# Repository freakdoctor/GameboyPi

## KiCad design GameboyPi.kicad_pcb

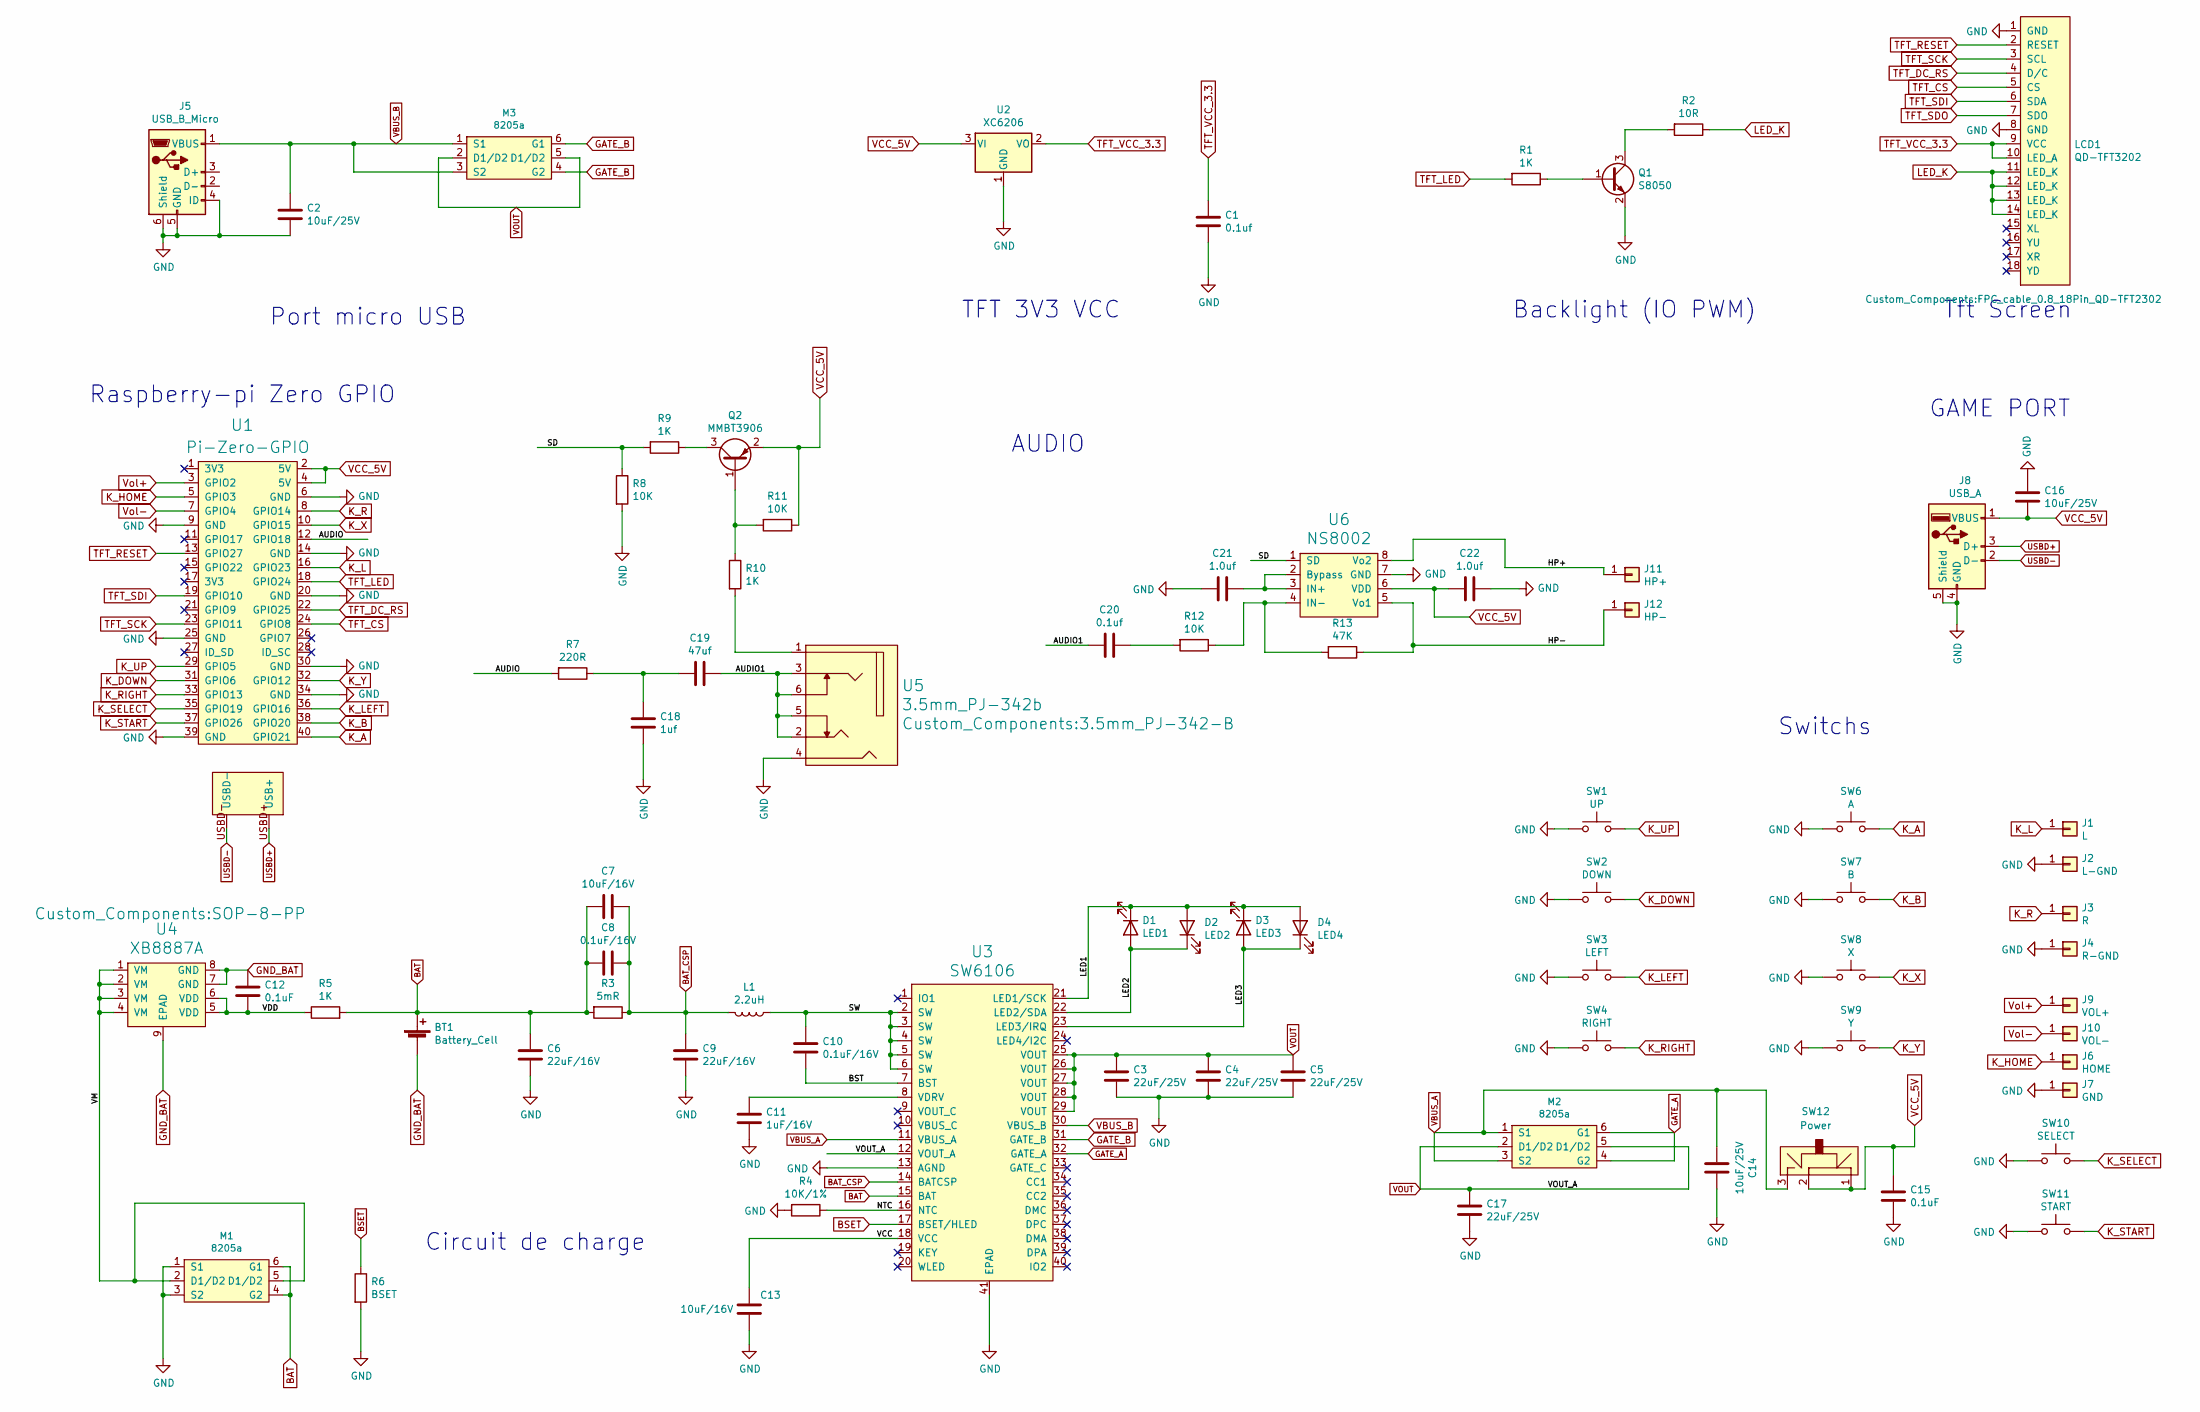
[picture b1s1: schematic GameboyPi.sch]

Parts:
BT1: Battery_Cell; Li-Po_3.7
C1: 0.1uf; C_0805_2012Metric; LCSC C286511
C2, C16: 10uF/25V; C_1206_3216Metric; LCSC C90538
C3, C4, C5, C17: 22uF/25V; C_0805_2012Metric; LCSC C90153
C6, C9: 22uF/16V; C_0805_2012Metric; LCSC C116973
C7, C13: 10uF/16V; C_0603_1608Metric; LCSC C70225
C8, C10: 0.1uF/16V; C_0603_1608Metric; LCSC C307478
C11: 1uF/16V; C_0603_1608Metric; LCSC C307478
C12: 0.1uF; C_0603_1608Metric; LCSC C307478
C14: 10uF/25V; C_1206_3216Metric; LCSC C70225
C15: 0.1uF; C_1206_3216Metric; LCSC C105213
C18: 1uf; C_0603_1608Metric
C19: 47uf; C_0603_1608Metric
C20: 0.1uf; C_0603_1608Metric
C21, C22: 1.0uf; C_0603_1608Metric
D1: LED1; LED_0805_2012Metric; LCSC C138557
D2: LED2; LED_0805_2012Metric; LCSC C138557
D3: LED3; LED_0805_2012Metric; LCSC C138557
D4: LED4; LED_0805_2012Metric; LCSC C138557
J1: L; Pin_D1.0mm_L10.0mm_LooseFit
J2: L-GND; Pin_D1.0mm_L10.0mm_LooseFit
J3: R; Pin_D1.0mm_L10.0mm_LooseFit
J4: R-GND; Pin_D1.0mm_L10.0mm_LooseFit
J5: USB_B_Micro; USB_Micro-B_Molex_47346-0001; LCSC C132560
J6: HOME; Edge_connection
J7: GND; Edge_connection
J8: USB_A; USB_A_Molex_67643_Horizontal; LCSC C2765194
J9: VOL+; Edge_connection
J10: VOL-; Edge_connection
J11: HP+; Edge_connection
J12: HP-; Edge_connection
L1: 2.2uH; L_Abracon_ASPI-0630LR
LCD1: QD-TFT3202; FPC_cable_0.8_18Pin_QD-TFT2302
M1, M2, M3: 8205a; SOT-23-6; LCSC C2762931
Q1: S8050; SOT-23; LCSC C2146
Q2: MMBT3906; SOT-23
R1: 1K; R_0805_2012Metric; LCSC C269744
R2: 10R; R_0805_2012Metric; LCSC C17477
R3: 5mR; R_1206_3216Metric; LCSC C601096
R4: 10K/1%; R_0603_1608Metric; LCSC C116677
R5: 1K; R_0603_1608Metric; LCSC C269704
R6: BSET; R_0805_2012Metric
R7: 220R; R_0603_1608Metric
R8, R11, R12: 10K; R_0603_1608Metric
R9, R10: 1K; R_0603_1608Metric
R13: 47K; R_0603_1608Metric
SW1: UP; Kbpad
SW2: DOWN; Kbpad
SW3: LEFT; Kbpad
SW4: RIGHT; Kbpad
SW6: A; Kbpad
SW7: B; Kbpad
SW8: X; Kbpad
SW9: Y; Kbpad
SW10: SELECT; Kbpad
SW11: START; Kbpad
SW12: Power; SW_SPDT_PCM12
U1: Pi-Zero-GPIO; Pi_Zero_SMD
U2: XC6206; SOT-23; LCSC C5446
U3: SW6106; QFN-40-1EP_6x6mm_P0.5mm_EP4.6x4.6mm_ThermalVias; LCSC C406803
U4: XB8887A; SOP-8-PP
U5: 3.5mm_PJ-342b; 3.5mm_PJ-342-B
U6: NS8002; SOP-8-PP

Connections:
/AUDIO: R7.2, U1.12 (GPIO18)
/AUDIO1: C19.1, C20.2, U5.2, U5.3, U5.5, U5.6
/BST: C10.1, U3.7 (BST)
/HP+: J11.1, U6.8 (Vo2); also elsewhere on the board
/HP-: J12.1, R13.1, U6.5 (Vo1); also elsewhere on the board
/LED1: D1.1 (K), D2.2 (A), D3.1 (K), D4.2 (A), U3.21 (LED1/SCK)
/LED2: D1.2 (A), D2.1 (K), U3.22 (LED2/SDA)
/LED3: D3.2 (A), D4.1 (K), U3.23 (LED3/IRQ)
/NTC: R4.1, U3.16 (NTC)
/SD: R8.1, R9.2, U6.1 (SD)
/SW: C10.2, L1.1, U3.2 (SW), U3.3 (SW), U3.4 (SW), U3.5 (SW), U3.6 (SW)
/VCC: C13.2, U3.18 (VCC)
/VDD: C12.2, R5.1, U4.5 (VDD), U4.6 (VDD)
/VM: M1.2 (D1/D2), M1.5 (D1/D2), U4.1 (VM), U4.2 (VM), U4.3 (VM), U4.4 (VM)
BAT: BT1.1 (+), C6.1, C7.2, C8.2, M1.4 (G2), M1.6 (G1), R3.2, R5.2, U3.15 (BAT); also elsewhere on the board
BAT_CSP: C7.1, C8.1, C9.1, L1.2, R3.1, U3.14 (BATCSP)
BSET: R6.1, U3.17 (BSET/HLED)
GATE_A: M2.4 (G2), M2.6 (G1), U3.32 (GATE_A)
GATE_B: M3.4 (G2), M3.6 (G1), U3.31 (GATE_B)
GND: C1.2, C2.2, C3.2, C4.2, C5.2, C6.2, C9.2, C11.2, C13.1, C14.1, C15.2, C16.1, C17.2, C18.1, C21.2, C22.1, J2.1, J4.1, J5.4 (ID), J5.5 (GND), J5.6 (Shield), J7.1, J8.4 (GND), J8.5 (Shield), LCD1.1 (GND), LCD1.8 (GND), M1.1 (S1), M1.3 (S2), Q1.2 (E), R4.2, R6.2, R8.2, SW1.1, SW2.1, SW3.1, SW4.1, SW6.1, SW7.1, SW8.1, SW9.1, SW10.1, SW11.1, U1.6 (GND), U1.9 (GND), U1.14 (GND), U1.20 (GND), U1.25 (GND), U1.30 (GND), U1.34 (GND), U1.39 (GND), U2.1 (GND), U3.13 (AGND), U3.41 (EPAD), U5.4, U6.7 (GND)
GND_BAT: BT1.2 (-), C12.1, U4.7 (GND), U4.8 (GND), U4.9 (EPAD); also elsewhere on the board
K_A: SW6.2, U1.40 (GPIO21)
K_B: SW7.2, U1.38 (GPIO20)
K_DOWN: SW2.2, U1.31 (GPIO6)
K_HOME: J6.1, U1.5 (GPIO3)
K_L: J1.1, U1.16 (GPIO23)
K_LEFT: SW3.2, U1.36 (GPIO16)
K_R: J3.1, U1.8 (GPIO14)
K_RIGHT: SW4.2, U1.33 (GPIO13)
K_SELECT: SW10.2, U1.35 (GPIO19)
K_START: SW11.2, U1.37 (GPIO26)
K_UP: SW1.2, U1.29 (GPIO5)
K_X: SW8.2, U1.10 (GPIO15)
K_Y: SW9.2, U1.32 (GPIO12)
LED_K: LCD1.11 (LED_K), LCD1.12 (LED_K), LCD1.13 (LED_K), LCD1.14 (LED_K), R2.1
unnamed: C11.1, U3.8 (VDRV)
unnamed: C18.2, C19.2, R7.1
unnamed: C20.1, R12.2
unnamed: C21.1, U6.2 (Bypass), U6.3 (IN+)
unnamed: Q1.1 (B), R1.1
unnamed: Q1.3 (C), R2.2
unnamed: Q2.1 (B), R10.1, R11.2
unnamed: Q2.3 (C), R9.1
unnamed: R10.2, U5.1
unnamed: R12.1, R13.2, U6.4 (IN-)
TFT_CS: LCD1.5 (CS), U1.24 (GPIO8)
TFT_DC_RS: LCD1.4 (D/C), U1.22 (GPIO25)
TFT_LED: R1.2, U1.18 (GPIO24)
TFT_RESET: LCD1.2 (RESET), U1.13 (GPIO27)
TFT_SCK: LCD1.3 (SCL), U1.23 (GPIO11)
TFT_SDI: LCD1.6 (SDA), U1.19 (GPIO10)
TFT_SDO: LCD1.7 (SDO)
TFT_VCC_3.3: C1.1, LCD1.9 (VCC), LCD1.10 (LED_A), U2.2 (VO)
USBD+: J8.3 (D+), U1.USBD+ (USB+)
USBD-: J8.2 (D-), U1.USBD-
VBUS_A: C14.2, M2.1 (S1), M2.3 (S2), SW12.3, U3.11 (VBUS_A)
VBUS_B: C2.1, J5.1 (VBUS), M3.1 (S1), M3.3 (S2), U3.30 (VBUS_B)
VCC_5V: C15.1, C16.2, C22.2, J8.1 (VBUS), Q2.2 (E), R11.1, SW12.1, SW12.2, U1.2 (5V), U1.4 (5V), U2.3 (VI), U6.6 (VDD)
VOUT: C3.1, C4.1, C5.1, C17.1, M2.2 (D1/D2), M2.5 (D1/D2), M3.2 (D1/D2), M3.5 (D1/D2), U3.12 (VOUT_A), U3.25 (VOUT), U3.26 (VOUT), U3.27 (VOUT), U3.28 (VOUT), U3.29 (VOUT)
Vol+: J9.1, U1.3 (GPIO2); also elsewhere on the board
Vol-: J10.1, U1.7 (GPIO4); also elsewhere on the board

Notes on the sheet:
TFT 3V3 VCC
Raspberry-pi Zero GPIO
Port micro USB
Circuit de charge
GAME PORT
Switchs
Backlight (IO PWM)
Tft Screen
AUDIO

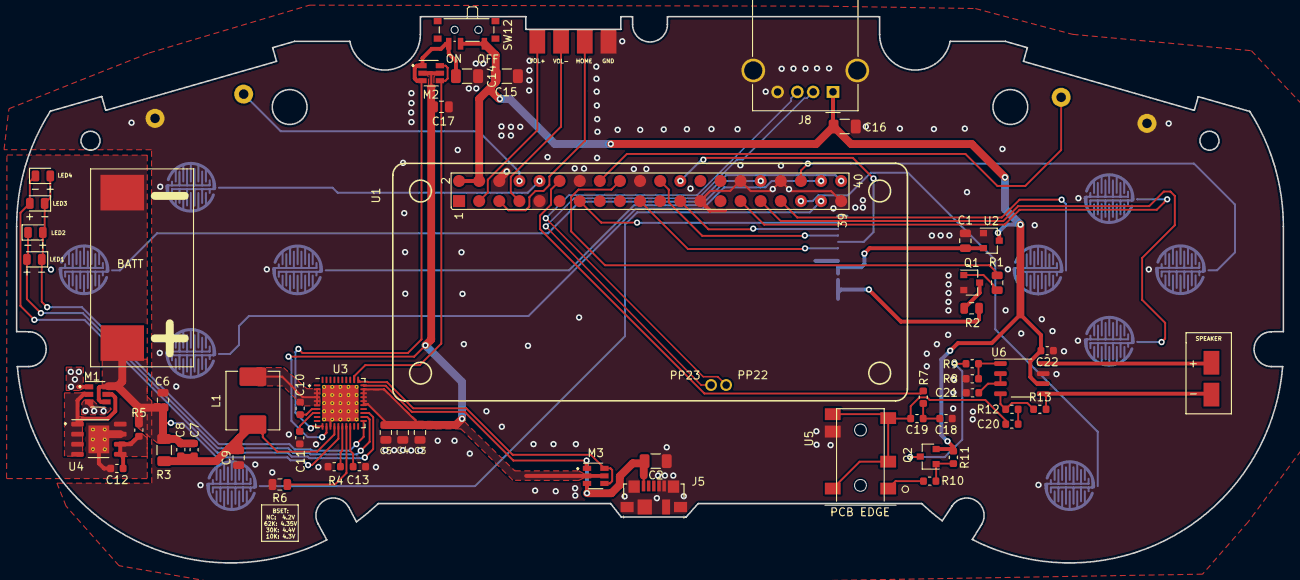
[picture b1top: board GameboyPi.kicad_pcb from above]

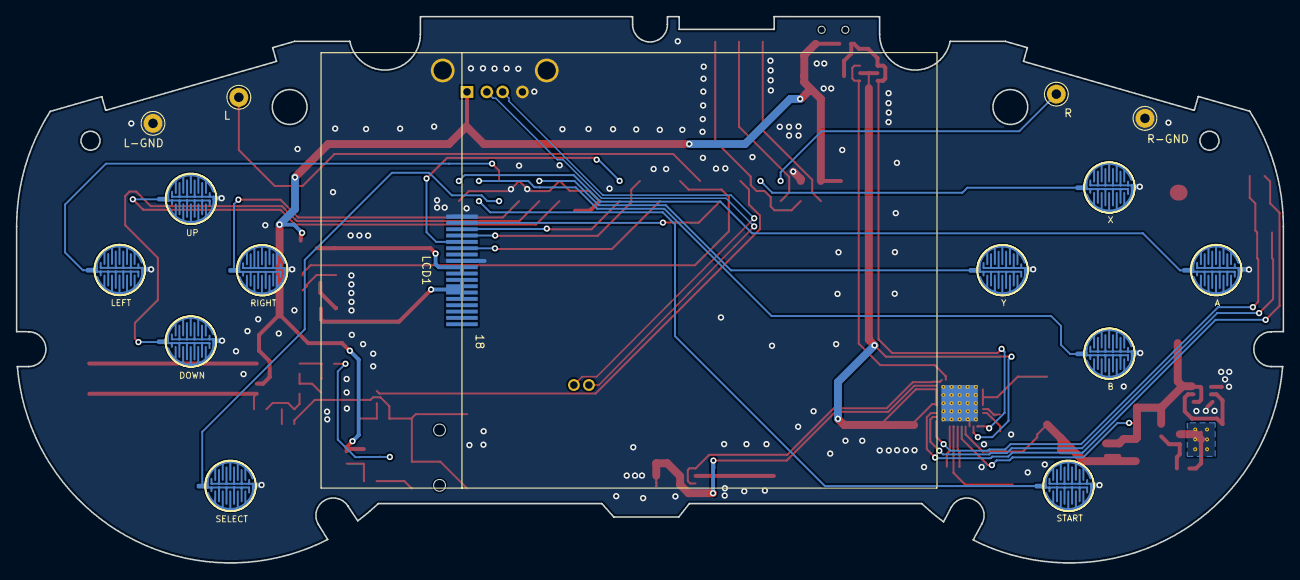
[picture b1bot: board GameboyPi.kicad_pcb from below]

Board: 2 copper layers, 160.0 x 69.0 mm, 76 parts (15 on the bottom side), 60 nets.

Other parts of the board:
+: HP+; Edge_connection
-: HP-; Edge_connection
BATT: Battery_Cell; Li-Po_3.7
VOL+: VOL+; Edge_connection
VOL-: VOL-; Edge_connection

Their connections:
/HP+: +.1; also elsewhere on the board
/HP-: -.1; also elsewhere on the board
BAT: BATT.1; also elsewhere on the board
GND_BAT: BATT.2; also elsewhere on the board
Vol+: VOL+.1; also elsewhere on the board
Vol-: VOL-.1; also elsewhere on the board

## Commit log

2022-04-14 SuperPiTendo
    SuperPiTendo
2022-04-23 maj kicad
